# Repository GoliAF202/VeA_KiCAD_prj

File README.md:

# VeA_KiCAD_prj

Kursa projektiem!

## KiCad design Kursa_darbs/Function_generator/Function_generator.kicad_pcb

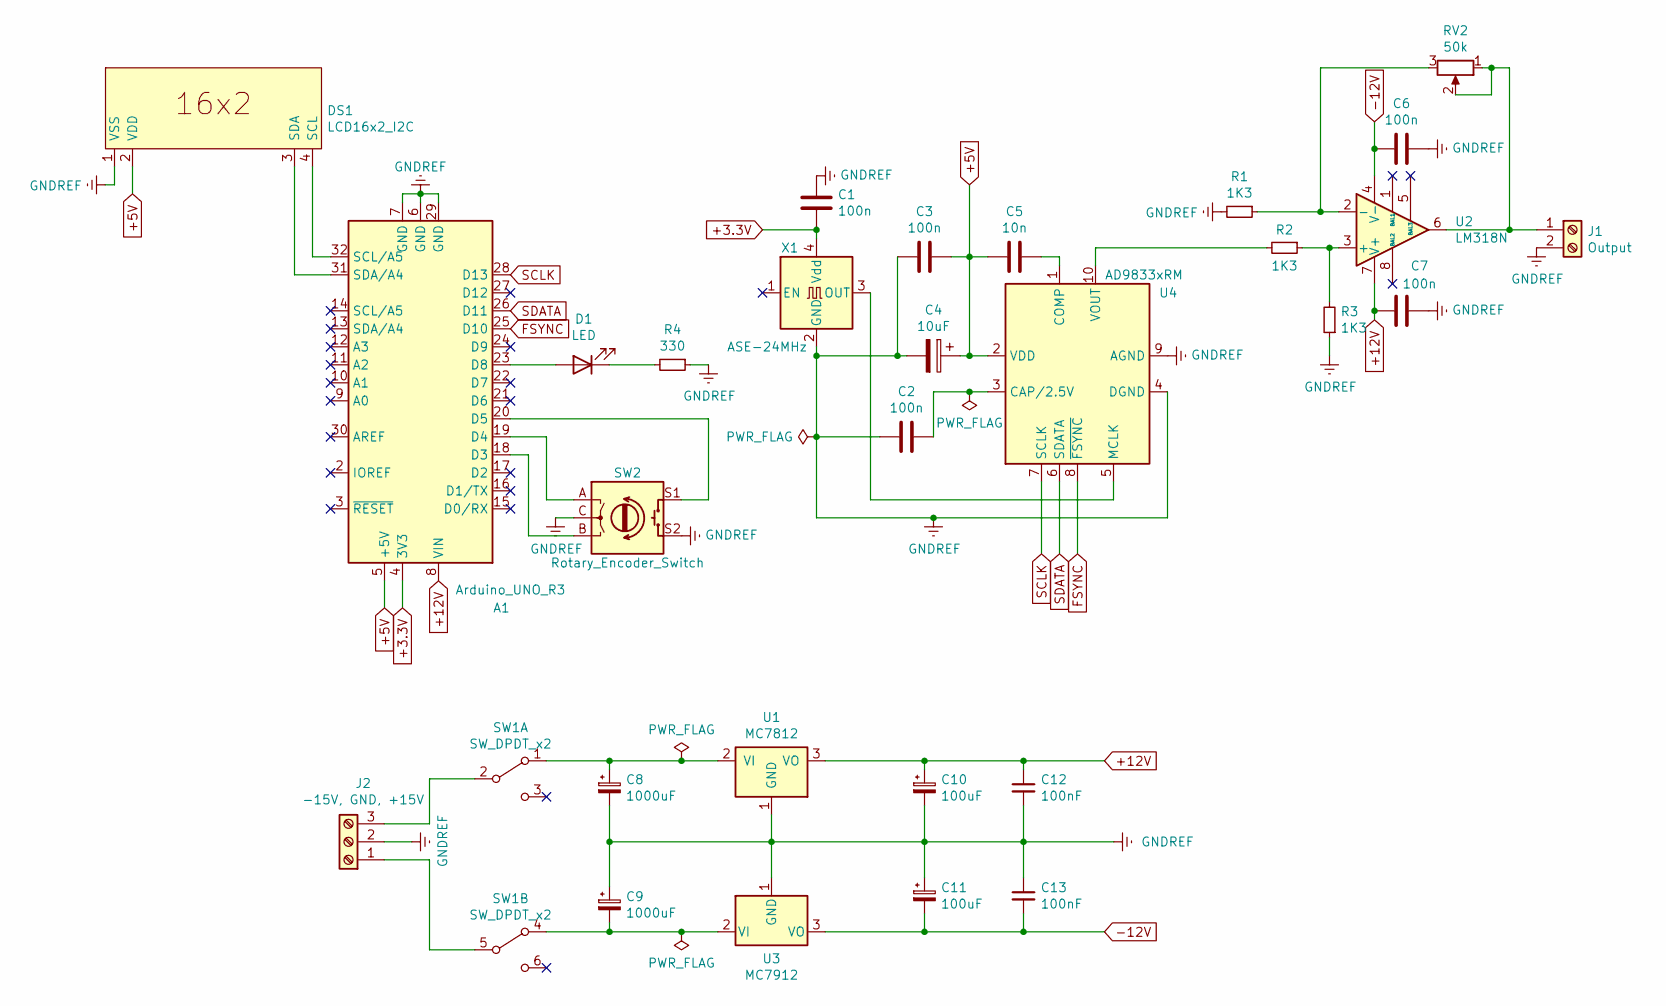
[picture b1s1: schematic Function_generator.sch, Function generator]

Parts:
A1: Arduino_UNO_R3
C1, C2, C3, C6, C7: 100n; C_0603_1608Metric_Pad1.08x0.95mm_HandSolder
C4: 10uF; CP_Elec_4x5.8
C5: 10n; C_0603_1608Metric_Pad1.08x0.95mm_HandSolder
C8, C9: 1000uF; Capacitor_mans
C10, C11: 100uF; CP_Elec_6.3x9.9
C12, C13: 100nF; C_0603_1608Metric_Pad1.08x0.95mm_HandSolder
D1: LED; LED_0603_1608Metric_Pad1.05x0.95mm_HandSolder
DS1: LCD16x2_I2C; PinHeader_1x04_P2.54mm_Vertical
J1: Output; PinHeader_1x02_P2.54mm_Vertical
J2: -15V, GND, +15V; PinHeader_1x03_P2.54mm_Vertical
R1, R2, R3: 1K3; R_0603_1608Metric_Pad0.98x0.95mm_HandSolder
R4: 330; R_0603_1608Metric_Pad0.98x0.95mm_HandSolder
RV2: 50k; Potentiometer_Bourns_3214W_Vertical
SW1: SW_DPDT_x2; SW_CuK_JS202011AQN_DPDT_Angled
SW2: Rotary_Encoder_Switch; RotaryEncoder_Alps_EC11E-Switch_Vertical_H20mm
U1: MC7812; TO-252-2
U2: LM318N; SOIC-8_3.9x4.9mm_P1.27mm
U3: MC7912; TO-263-2
U4: AD9833xRM; MSOP-10_3x3mm_P0.5mm
X1: ASE-24MHz; Oscillator_SMD_Abracon_ASE-4Pin_3.2x2.5mm

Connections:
+3.3V: A1.4 (3V3), C1.2, X1.4 (Vdd)
+5V: A1.5 (+5V), C3.1, C4.1, C5.2, DS1.2 (VDD), U4.2 (VDD)
+12V: A1.8 (VIN), C7.2, C10.1, C12.1, U1.3 (VO), U2.7 (V+)
-12V: C6.2, C11.2, C13.2, U2.4 (V-), U3.3 (VO)
FSYNC: A1.25 (D10), U4.8 (~FSYNC)
GNDREF: A1.6 (GND), A1.7 (GND), A1.29 (GND), C1.1, C2.2, C3.2, C4.2, C6.1, C7.1, C8.2, C9.1, C10.2, C11.1, C12.2, C13.1, DS1.1 (VSS), J1.2, J2.2, R1.2, R3.1, R4.1, SW2.C, SW2.S2, U1.1 (GND), U3.1 (GND), U4.4 (DGND), U4.9 (AGND), X1.2 (GND)
unnamed: A1.18 (D3), SW2.B
unnamed: A1.19 (D4), SW2.A
unnamed: A1.20 (D5), SW2.S1
unnamed: A1.23 (D8), D1.2 (A)
unnamed: A1.31 (SDA/A4), DS1.3 (SDA)
unnamed: A1.32 (SCL/A5), DS1.4 (SCL)
unnamed: C2.1, U4.3 (CAP/2.5V)
unnamed: C5.1, U4.1 (COMP)
unnamed: C8.1, SW1.1 (A), U1.2 (VI)
unnamed: C9.2, SW1.4 (A), U3.2 (VI)
unnamed: D1.1 (K), R4.2
unnamed: J1.1, RV2.1, RV2.2, U2.6
unnamed: J2.1, SW1.5 (B)
unnamed: J2.3, SW1.2 (B)
unnamed: R1.1, RV2.3, U2.2 (-)
unnamed: R2.1, R3.2, U2.3 (+)
unnamed: R2.2, U4.10 (VOUT)
unnamed: U4.5 (MCLK), X1.3 (OUT)
SCLK: A1.28 (D13), U4.7 (SCLK)
SDATA: A1.26 (D11), U4.6 (SDATA)

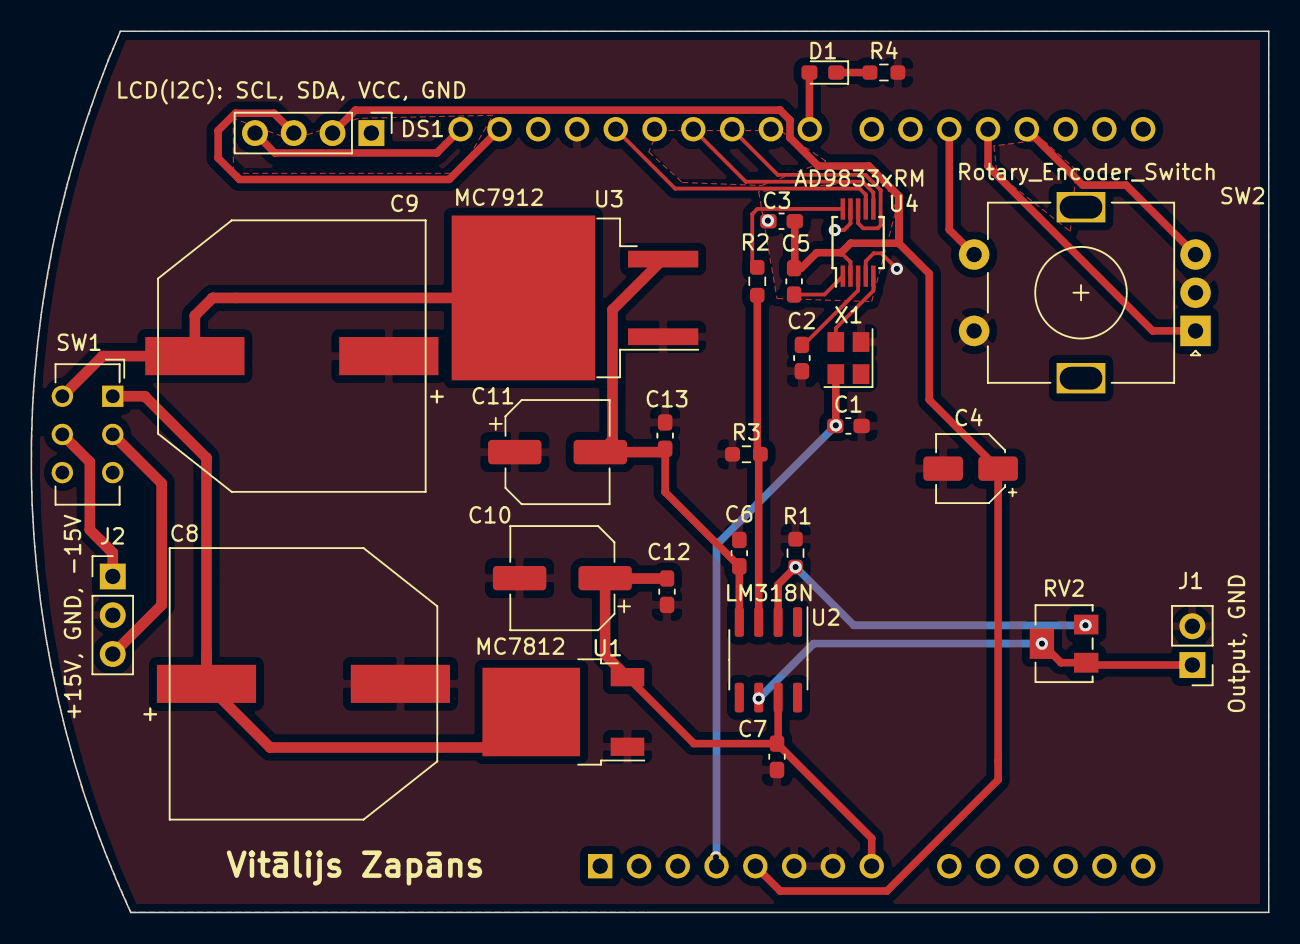
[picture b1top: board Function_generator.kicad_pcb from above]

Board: 2 copper layers, 81.0 x 57.7 mm, 30 parts (1 on the bottom side), 26 nets.

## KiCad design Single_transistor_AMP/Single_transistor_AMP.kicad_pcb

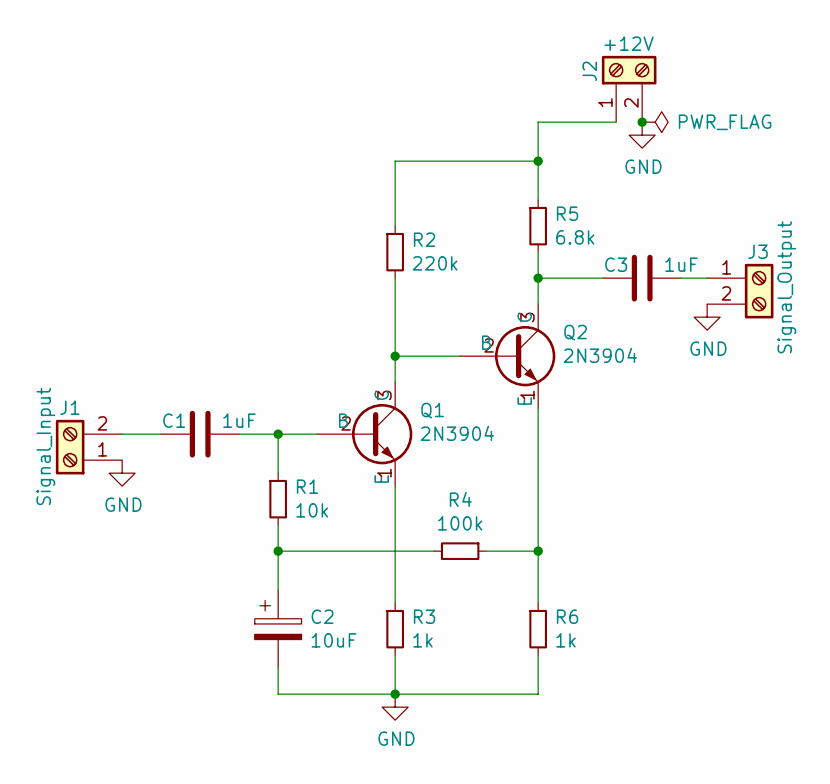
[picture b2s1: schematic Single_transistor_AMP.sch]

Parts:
C1, C3: 1uF; C_0805_2012Metric
C2: 10uF; CP_Elec_4x3
J1: Signal_Input; PinHeader_1x02_P2.54mm_Vertical
J2: +12V; PinHeader_1x02_P2.54mm_Vertical
J3: Signal_Output; PinHeader_1x02_P2.54mm_Vertical
Q1, Q2: 2N3904; TO-92_Inline
R1: 10k; R_0805_2012Metric_Pad1.20x1.40mm_HandSolder
R2: 220k; R_0805_2012Metric_Pad1.20x1.40mm_HandSolder
R3, R6: 1k; R_0805_2012Metric_Pad1.20x1.40mm_HandSolder
R4: 100k; R_0805_2012Metric_Pad1.20x1.40mm_HandSolder
R5: 6.8k; R_0805_2012Metric_Pad1.20x1.40mm_HandSolder

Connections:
GND: C2.2, J1.1, J2.2, J3.2, R3.2, R6.2
unnamed: C1.1, Q1.2 (B), R1.1
unnamed: C1.2, J1.2
unnamed: C2.1, R1.2, R4.2
unnamed: C3.1, J3.1
unnamed: C3.2, Q2.3 (C), R5.2
unnamed: J2.1, R2.1, R5.1
unnamed: Q1.1 (E), R3.1
unnamed: Q1.3 (C), Q2.2 (B), R2.2
unnamed: Q2.1 (E), R4.1, R6.1

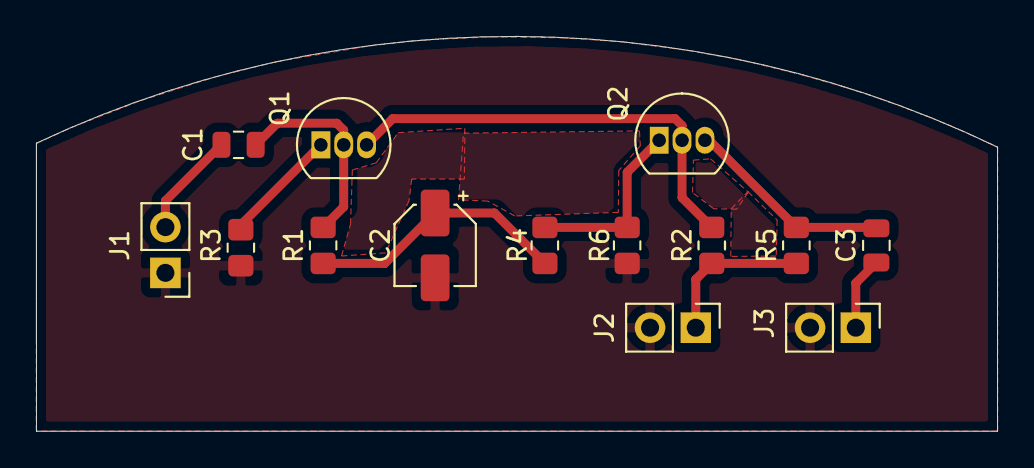
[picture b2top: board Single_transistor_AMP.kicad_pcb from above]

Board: 2 copper layers, 53.4 x 21.9 mm, 14 parts (0 on the bottom side), 10 nets.

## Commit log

2020-09-22 README tika veiktas izmainas
2020-10-07 Otrais majas darbs
2020-10-07 Izmainiju nosaukumu
2020-10-13 Tresais majas darbs
2020-10-15 Ceturtais majas darbs
2020-10-27 Piekta majas darba treninuzdevums
2020-10-27 Piektais majas darbs
2020-10-27 Nodzesu kaut ko
2020-10-28 Sestais majas darbs
2020-11-18 Septitajs majas darbs
2020-12-08 Astotais majas darbs
2020-12-08 Devitais majas darbs
2020-12-09 Desmitajs majas darbs
2021-01-23 Kursa darbs, Vitālijs Zapāns
